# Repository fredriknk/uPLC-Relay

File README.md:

# μPLC-Relay
### Pcbway Sponsorship
Thanks so much to [PCBWay](https://www.pcbway.com/) who offered to assemble my first prototype batch of all three [uPLC modules](https://github.com/fredriknk/uPLC-stack). They deliver awesome quality as always, see the result for yourself below.

 I now have two prototypes of the uPLC-Relay so ESP-Home integrations will come soon.

ESP micro PLC the size of a post stamp. he uPLC-relay version  has two small signal relay module utilizing an [ESP-32-C3](./DOCUMENTATION/esp-12f_product_specification_en.pdf) wifi, bluetooth module for communication and MCU, it has a 0-24V buck regulator, has two 2.5-25V inputs, two 25v, 100/50ma high speed open drain output through a [TBD062003](./DOCUMENTATION/2304140030_TOSHIBA-TBD62003AFWG_C114084.pdf) DMOS transistor array ic. And two relay outputs are capable of driving around 25V 500ma. 

Thanks to [u/PricelessToolkit/ESPClicker](https://github.com/PricelessToolkit/ESPClicker) for inspiration.

[Schematic](./DOCUMENTATION/_schematic.pdf)

[Assembly IBOM](https://htmlpreview.github.io/?https://raw.githubusercontent.com/fredriknk/uplc/main/DOCUMENTATION/ibom.html)

## Specifications
| **Parameter**   | **Description**                                                     |
|-----------------|---------------------------------------------------------------------|
| _Input voltage_ | 3.8-24v                               |
| _Current_       | TBD Wifi: ##mA, Radio Off: ##mA, Deep sleep ##uA |  
| _Communication_ | 2.4ghz WIFI, Uart TTL                            |
| _Baudrate_      | 115200                                                              |
| _PCB size_      | 22x31.1mm                                                             |
| _PCB info_      | 1.6mm FR4, HASL lead free, 4 layer               |
| _Case size_     | XxXxXmm TBD                                                         |

## Connector

| **Label**   | **GPIO**|**Description**       |
|------------|-----|-------------------------|
|_R2NO_ | GPIO5 | Relay 1 Normally Open |
|_R2CO_ | GPIO5  | Relay 1 COM |
|_R2NC_ | GPIO5 | Relay 1 Normally Closed |
|_R1NO_ | GPIO6 | Relay 1 Normally Open |
|_R1CO_ | GPIO6  | Relay 1 COM |
|_R1NC_ | GPIO6 | Relay 1 Normally Closed |
|_HI2_ | GPIO19 | 2.5-25v input |
|_HI1_ | GPIO18 | 2.5-25v input |
|_HO2_ | GPIO3 | 25v 50ma open drain output |
|_HO1_ | GPIO7 | 25v 100ma open drain output |
|_4-24V_ | 3V3 |4-24v |
|_GND_ | GND |  Ground  |

## PCB Pictures
PCB assembly by [PCBWay](https://www.pcbway.com/)

## Homeassistant Implementation
TODO

## FIRST PRODUCTION PROTOTYPE
TODO

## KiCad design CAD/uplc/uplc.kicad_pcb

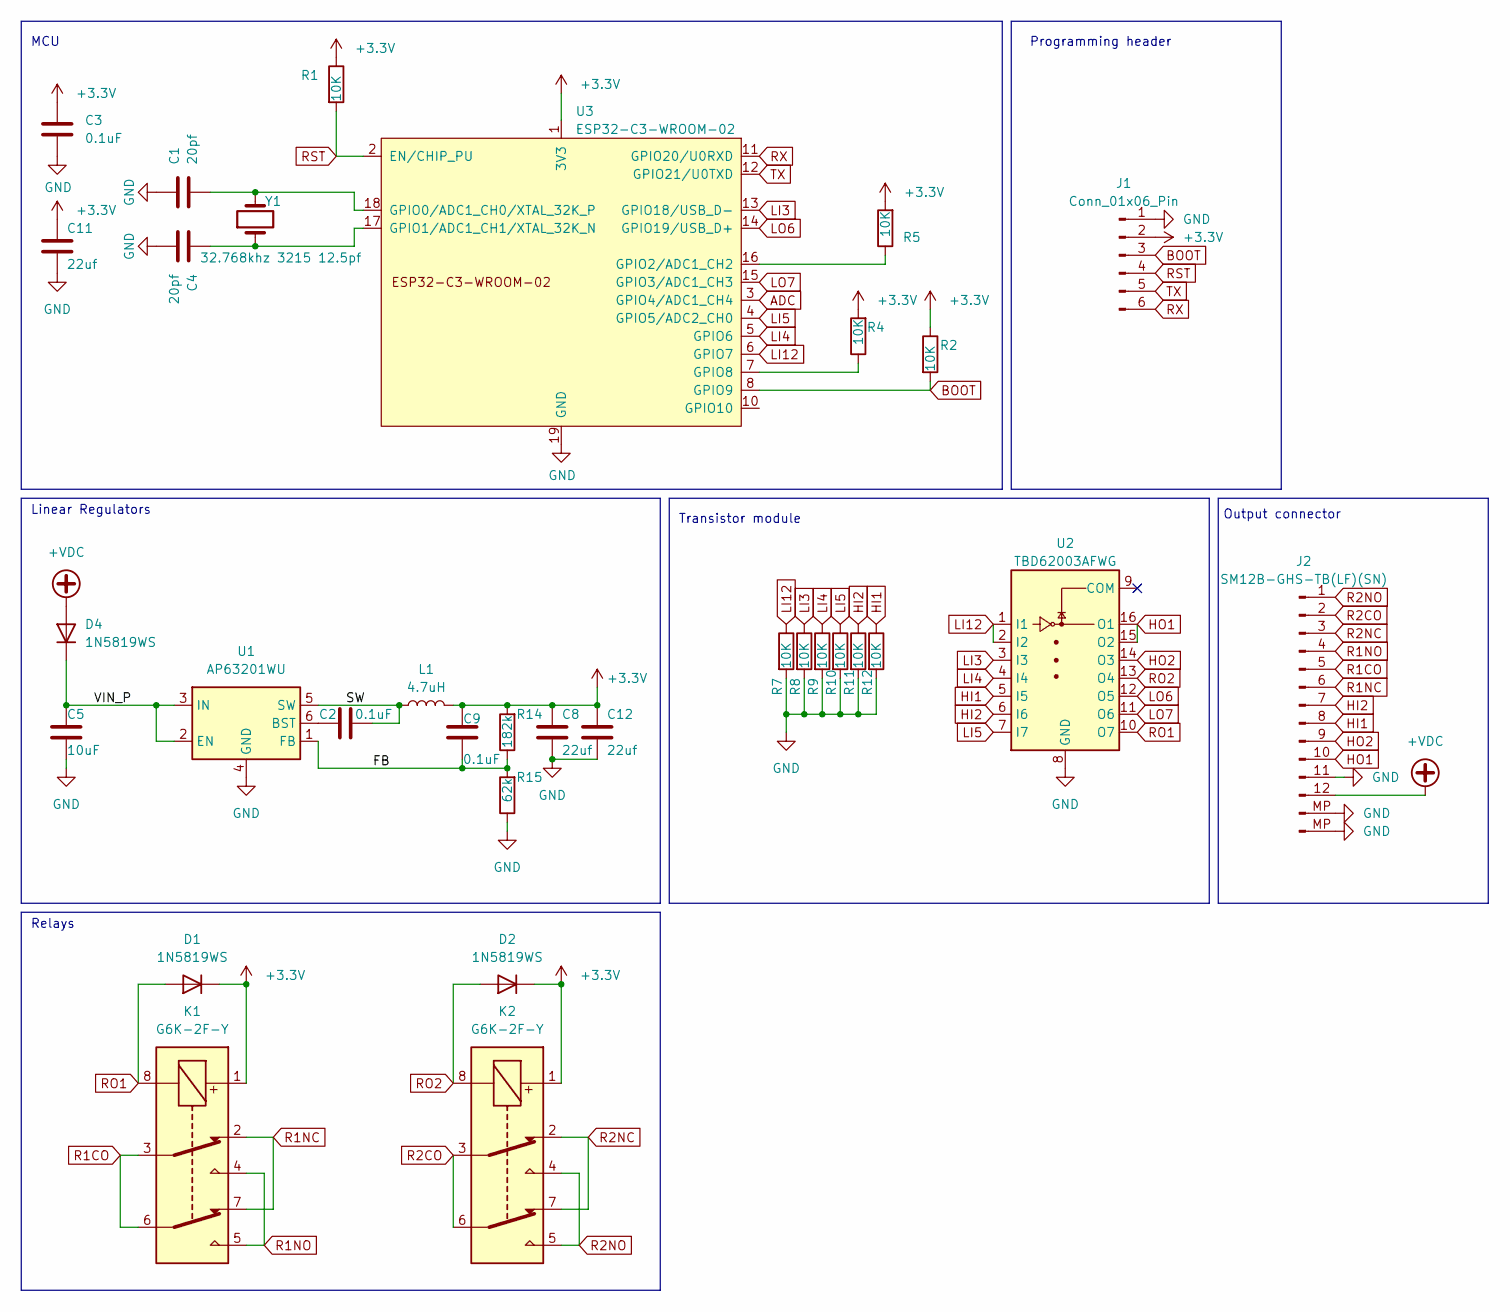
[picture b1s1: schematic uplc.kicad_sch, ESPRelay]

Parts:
C1, C4: 20pf; C_0402_1005Metric; MPN 0402CG200J500NT; LCSC Part # C1554
C2, C3, C9: 0.1uF; C_0402_1005Metric; MPN GRM155R71H104KE14D; LCSC Part # C77020
C5: 10uF; C_0805_2012Metric; MPN GRM21BR6YA106KE43L; LCSC Part # C162422
C8, C11, C12: 22uf; C_0402_1005Metric; MPN GRM155R60J226ME11D; LCSC Part # C415703
D1, D2, D4: 1N5819WS; D_SOD-323; MPN 1N5819WS; LCSC Part # C191023
J1: Conn_01x06_Pin; TestPoint_Pad_1.0x1.0mm_6pad; LCSC Part # DNP
J2: SM12B-GHS-TB(LF)(SN); JST_GH_SM12B-GHS-TB_1x12-1MP_P1.25mm_Horizontal; MPN SM12B-GHS-TB(LF)(SN); LCSC Part # C265421
K1, K2: G6K-2F-Y; Relay_DPDT_Omron_G6K-2F-Y; MPN G6K-2F-Y DC3; LCSC Part # C93168
L1: 4.7uH; L_1008_2520Metric; MPN LQM2HPN4R7MG0L; LCSC Part # C82314
R1, R2, R4, R5, R7, R8, R9, R10, R11, R12: 10K; R_0402_1005Metric; MPN 0402WGF1002TCE; LCSC Part # C25744
R14: 182k; R_0402_1005Metric; MPN 0402WGF1823TCE; LCSC Part # C11481
R15: 62k; R_0402_1005Metric; MPN RC0402FR-0762KL; LCSC Part # C137950
U1: AP63201WU; TSOT-23-6; MPN AP63201WU-7; LCSC Part # C2071044
U2: TBD62003AFWG; SOIC-16_3.9x9.9mm_P1.27mm; MPN TBD62003AFWG; LCSC Part # C114084
U3: ESP32-C3-WROOM-02; MPN ESP32-C3-WROOM-02-N4; LCSC Part # C2934560
Y1: 32.768khz 3215 12.5pf; Crystal_SMD_3215-2Pin_3.2x1.5mm; MPN Q13FC13500004; LCSC Part # C32346

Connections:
+3.3V: C3.1, C8.1, C9.1, C11.1, C12.1, D1.1 (K), D2.1 (K), J1.2, K1.1, K2.1, L1.2, R1.1, R2.1, R4.2, R5.2, R14.2, U3.1 (3V3)
+VDC: D4.2 (A), J2.12
/FB: C9.2, R14.1, R15.2, U1.1 (FB)
/SW: C2.1, L1.1, U1.5 (SW)
/VIN_P: C5.1, D4.1 (K), U1.2 (EN), U1.3 (IN)
ADC: U3.3 (GPIO4/ADC1_CH4)
BOOT: J1.3, R2.2, U3.8 (GPIO9)
GND: C1.1, C3.2, C4.2, C5.2, C8.2, C11.2, C12.2, J1.1, J2.11, J2.MP (Pin_13), R7.2, R8.2, R9.2, R10.2, R11.2, R12.2, R15.1, U1.4 (GND), U2.8 (GND), U3.9 (GND), U3.19 (GND)
HI1: J2.8, R12.1, U2.5 (I5)
HI2: J2.7, R11.1, U2.6 (I6)
HO1: J2.10, U2.15 (O2), U2.16 (O1)
HO2: J2.9, U2.14 (O3)
LI3: R8.1, U2.3 (I3), U3.13 (GPIO18/USB_D-)
LI4: R9.1, U2.4 (I4), U3.5 (GPIO6)
LI5: R10.1, U2.7 (I7), U3.4 (GPIO5/ADC2_CH0)
LI12: R7.1, U2.1 (I1), U2.2 (I2), U3.6 (GPIO7)
LO6: U2.12 (O5), U3.14 (GPIO19/USB_D+)
LO7: U2.11 (O6), U3.15 (GPIO3/ADC1_CH3)
unnamed: C2.2, U1.6 (BST)
unnamed: C1.2, U3.18 (GPIO0/ADC1_CH0/XTAL_32K_P), Y1.2
unnamed: C4.1, U3.17 (GPIO1/ADC1_CH1/XTAL_32K_N), Y1.1
unnamed: R5.1, U3.16 (GPIO2/ADC1_CH2)
unnamed: R4.1, U3.7 (GPIO8)
R1CO: J2.5, K1.3, K1.6
R1NC: J2.6, K1.2, K1.7
R1NO: J2.4, K1.4, K1.5
R2CO: J2.2, K2.3, K2.6
R2NC: J2.3, K2.2, K2.7
R2NO: J2.1, K2.4, K2.5
RO1: D1.2 (A), K1.8, U2.10 (O7)
RO2: D2.2 (A), K2.8, U2.13 (O4)
RST: J1.4, R1.2, U3.2 (EN/CHIP_PU)
RX: J1.6, U3.11 (GPIO20/U0RXD)
TX: J1.5, U3.12 (GPIO21/U0TXD)

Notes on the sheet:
Transistor module
Linear Regulators
MCU
Output connector
Programming header
Relays

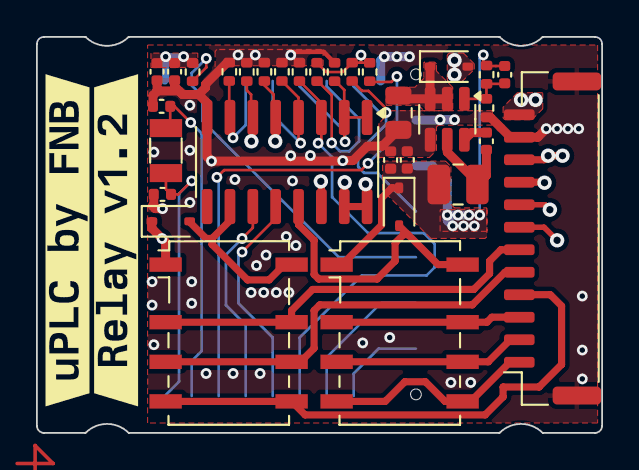
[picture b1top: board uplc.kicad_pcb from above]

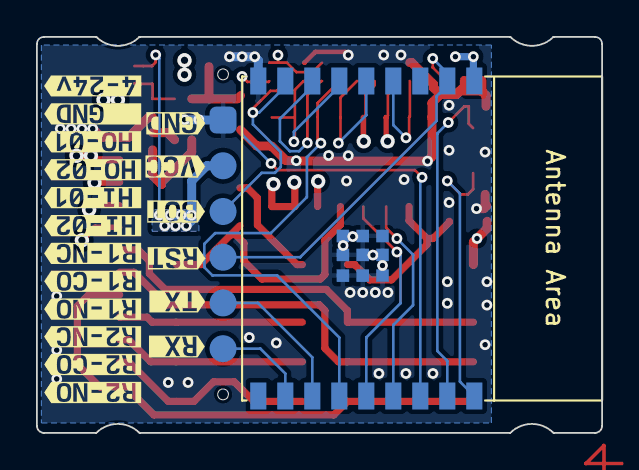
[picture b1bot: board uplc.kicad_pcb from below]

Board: 4 copper layers, 31.4 x 22.0 mm, 53 parts (20 on the bottom side), 33 nets.

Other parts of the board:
kibuzzard-65D6FF37: G***; kibuzzard-65D6FF37
kibuzzard-65D361A7: G***; kibuzzard-65D361A7
kibuzzard-65D361B0: G***; kibuzzard-65D361B0
kibuzzard-65D361D3: G***; kibuzzard-65D361D3
kibuzzard-65D361E1: G***; kibuzzard-65D361E1
kibuzzard-65D361E9: G***; kibuzzard-65D361E9
kibuzzard-65D361F2: G***; kibuzzard-65D361F2
kibuzzard-65D361FD: G***; kibuzzard-65D361FD
kibuzzard-65D460A0: G***; kibuzzard-65D460A0
kibuzzard-65D3616E: G***; kibuzzard-65D3616E
kibuzzard-65D3619D: G***; kibuzzard-65D3619D
kibuzzard-65D3620E: G***; kibuzzard-65D3620E
kibuzzard-65D7176D: G***; kibuzzard-65D7176D
kibuzzard-65D7177B: G***; kibuzzard-65D7177B
kibuzzard-65D36177: G***; kibuzzard-65D36177
kibuzzard-65D36206: G***; kibuzzard-65D36206
kibuzzard-65D46022: G***; kibuzzard-65D46022
kibuzzard-65D46066: G***; kibuzzard-65D46066
kibuzzard-65D49092: G***; kibuzzard-65D49092
kibuzzard-65D71774: G***; kibuzzard-65D71774

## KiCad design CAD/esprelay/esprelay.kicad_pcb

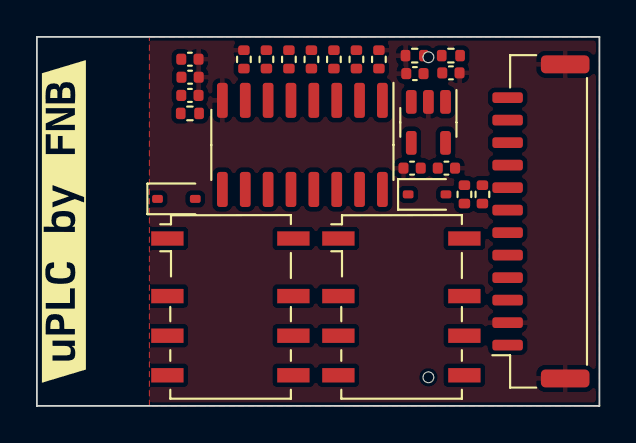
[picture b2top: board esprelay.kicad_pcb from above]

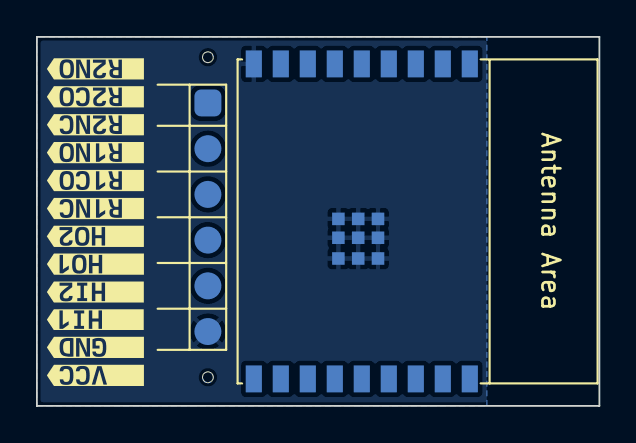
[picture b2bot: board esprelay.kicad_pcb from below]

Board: 2 copper layers, 31.2 x 20.5 mm, 41 parts (14 on the bottom side), 29 nets, no tracks yet.

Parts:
C1, C7, C11: 1uF; C_0402_1005Metric
C3, C4, C9, C10: 0.1uF; C_0402_1005Metric
D1, D2: 1N4148WS; D_SOD-323
J1: Conn_01x06_Pin; TestPoint_Pad_1.0x1.0mm_6pad
J2: SM12B-GHS-TB(LF)(SN); JST_GH_SM12B-GHS-TB_1x12-1MP_P1.25mm_Horizontal
K1, K2: G6K-2F-Y; Relay_DPDT_Omron_G6K-2F-Y
R1, R2, R4, R5, R7, R8, R9, R10, R11, R12: 10K; R_0402_1005Metric
R3: 13.7k; R_0402_1005Metric
R6: 316k; R_0402_1005Metric
U1: DS8242-33S5; SOT-23-5
U3: ESP32-C3-WROOM-02
U5: TBD62003AFWG; SOIC-16_3.9x9.9mm_P1.27mm
kibuzzard-65CFDA91: G***; kibuzzard-65CFDA91
kibuzzard-65CFDAA0: G***; kibuzzard-65CFDAA0
kibuzzard-65CFDAA7: G***; kibuzzard-65CFDAA7
kibuzzard-65CFDAAD: G***; kibuzzard-65CFDAAD
kibuzzard-65CFDAB5: G***; kibuzzard-65CFDAB5
kibuzzard-65CFDABC: G***; kibuzzard-65CFDABC
kibuzzard-65D272D8: G***; kibuzzard-65D272D8
kibuzzard-65666C6B: G***; kibuzzard-65666C6B
kibuzzard-65666C7B: G***; kibuzzard-65666C7B
kibuzzard-65666C71: G***; kibuzzard-65666C71
kibuzzard-65666C76: G***; kibuzzard-65666C76
kibuzzard-65666C87: G***; kibuzzard-65666C87
kibuzzard-65666CB7: G***; kibuzzard-65666CB7

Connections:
+3.3V: C3.1, C7.1, C9.1, C10.1, C11.1, J1.1, R1.1, R2.1, R4.2, R5.2, U1.5 (OUT), U3.1 (3V3)
+VDC: C1.1, C4.2, J2.1, R6.1, U1.1 (IN)
ADC: R3.1, R6.2, U3.18 (GPIO0/ADC1_CH0/XTAL_32K_P)
BOOT: J1.4, R2.2, U3.8 (GPIO9)
GND: C1.2, C3.2, C4.1, C7.2, C9.2, C10.2, C11.2, J1.6, J2.2, J2.MP (Pin_13), R3.2, R7.2, R8.2, R9.2, R10.2, R11.2, R12.2, U1.2 (GND), U3.9 (GND), U3.19 (GND), U5.8 (GND)
GPIO4: U3.15 (GPIO3/ADC1_CH3), U5.11 (O6)
GPIO5: U3.3 (GPIO4/ADC1_CH4), U5.10 (O7)
GPIO12: R8.1, U3.4 (GPIO5/ADC2_CH0), U5.3 (I3)
GPIO13: R7.1, U3.5 (GPIO6), U5.1 (I1), U5.2 (I2)
GPIO14: R9.1, U3.6 (GPIO7), U5.4 (I4)
GPIO15: R10.1, U3.10 (GPIO10), U5.5 (I5)
HI1: J2.3, R12.1, U5.6 (I6)
HI2: J2.4, R11.1, U5.7 (I7)
HO1: J2.5, U5.15 (O2), U5.16 (O1)
HO2: J2.6, U5.14 (O3)
unnamed: R5.1, U3.16 (GPIO2/ADC1_CH2)
unnamed: R4.1, U3.7 (GPIO8)
R1CO: J2.8, K1.3, K1.6
R1NC: J2.7, K1.2, K1.7
R1NO: J2.9, K1.4, K1.5
R2CO: J2.11, K2.3, K2.6
R2NC: J2.10, K2.2, K2.7
R2NO: J2.12, K2.4, K2.5
RO1: D1.2 (A), K1.8, U5.13 (O4)
RO2: D2.2 (A), K2.8, U5.12 (O5)
RST: J1.5, R1.2, U3.2 (EN/CHIP_PU)
RX: J1.3, U3.11 (GPIO20/U0RXD)
TX: J1.2, U3.12 (GPIO21/U0TXD)
VBUS: D1.1 (K), D2.1 (K), K1.1, K2.1

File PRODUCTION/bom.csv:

Designator,Footprint,Quantity,Value,LCSC Part #
"C1, C4",0402,2,20pf,C1554
"C10, C3, C5, C6, C9",0402,5,0.1uF,C307331
"C11, C2, C7",0402,3,1uF,C52923
"D1, D2, D3",D_SOD-323,3,1N5819WS,C191023
J1,TestPoint_Pad_1.0x1.0mm_6pad,1,Conn_01x06_Pin,
J2,JST_GH_SM12B-GHS-TB_1x12-1MP_P1.25mm_Horizontal,1,SM12B-GHS-TB(LF)(SN),C265421
"K1, K2",Relay_DPDT_Omron_G6K-2F-Y,2,G6K-2F-Y,C2982926
"R1, R10, R11, R12, R2, R4, R5, R7, R8, R9",0402,10,10K,C25744
R13,0402,1,1M,DNP
R3,0402,1,13.7k,C25854
R6,0402,1,316k,C25777
U1,SOT-23-5,1,DS8242-33S5,C5884133
U3,ESP32-C3-WROOM-02,1,ESP32-C3-WROOM-02,C2934560
U5,SOIC-16_3.9x9.9mm_P1.27mm,1,TBD62003AFWG,C114084
Y1,Crystal_SMD_3215-2Pin_3.2x1.5mm,1,32.568khz 3.2x1.5 12.5pf,C32346

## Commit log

2024-02-19 hardfork
2024-02-19 Hardfork esprelay
2024-02-19 RTC insert
2024-02-19 Pin Rearangement
2024-02-20 Rev 1.0
2024-02-20 Readme
2024-02-20 Gitignore lck update
2024-02-20 Readme ibom update
2024-02-20 Readme ibom link
2024-02-20 saving
2024-02-20 Readme edit
2024-02-21 Value updates
2024-02-21 rev 1.1
2024-02-22 Rev 1.2
2024-02-22 Production push rev 1.2
2024-02-22 Forgot schem and drawing
2024-02-22 Pictures
2024-02-22 Update rev nr
2024-10-14 Panelization changes
2025-04-09 Feat: Picture update
